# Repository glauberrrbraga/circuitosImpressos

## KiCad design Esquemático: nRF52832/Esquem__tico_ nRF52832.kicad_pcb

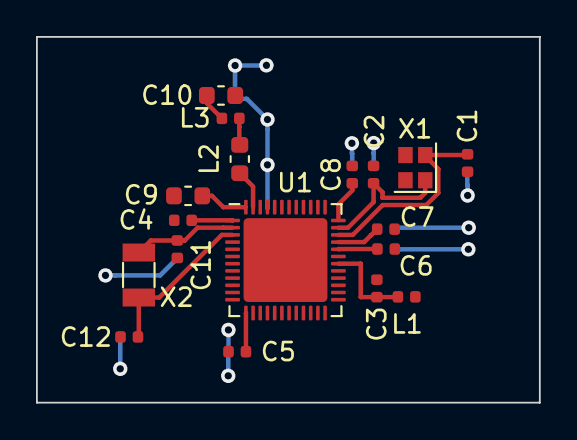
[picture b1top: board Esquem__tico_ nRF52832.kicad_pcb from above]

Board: 2 copper layers, 27.9 x 20.3 mm, 18 parts (0 on the bottom side), 13 nets.

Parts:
C1, C2, C11, C12: 12p; C_0402_1005Metric
C3: 0.8p; C_0402_1005Metric
C4, C5, C8: 100n; C_0402_1005Metric
C6: N.C.; C_0402_1005Metric
C7: 100p; C_0402_1005Metric
C9: 4.7µ; C_0603_1608Metric
C10: 1.0µ; C_0603_1608Metric
L1: 3.9nH; L_0402_1005Metric
L2: 10µ; L_0603_1608Metric
L3: 15n; L_0402_1005Metric
U1: nRF52832; QFN-48-1EP_6x6mm_P0.4mm_EP4.66x4.66mm
X1: 32MHz; Crystal_SMD_2016-4Pin_2.0x1.6mm
X2: 32.768kHz; Crystal_SMD_3215-2Pin_3.2x1.5mm

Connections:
Earth: C1.2, C2.2, C3.2, C4.2, C5.2, C6.2, C7.2, C8.2, C9.2, C10.2, C11.2, C12.2, U1.31, U1.45
unnamed: C1.1, U1.34, X1.2
unnamed: C2.1, U1.35, X1.1
unnamed: C3.1, L1.1, U1.30
unnamed: C4.1, U1.1
unnamed: C6.1, U1.32
unnamed: C7.1, U1.33
unnamed: C10.1, L3.1, U1.46
unnamed: C11.1, U1.2, X2.1
unnamed: C12.1, U1.3, X2.2
unnamed: L2.1, L3.2
unnamed: L2.2, U1.47
VDD: C5.1, C8.1, C9.1, U1.13, U1.36, U1.48
